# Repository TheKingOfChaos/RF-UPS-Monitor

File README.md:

# RF-UPS-Monitor

A mains power monitor built on a Raspberry Pi Pico with a W5500 Ethernet module. It reports whether mains power is present over SNMP v1 and v2c, including traps, together with standard interface statistics (IF-MIB) and the board temperature, so it can be monitored by LibreNMS or any other SNMP manager. It is configured through a menu on the USB serial port.

Current version: **2.4.2** (see [CHANGELOG.md](CHANGELOG.md)).

## Overview

- **Mains side:** an isolated detector (optocoupler with filtering) turns mains presence into a clean 3.3 V level on GPIO27. In the test setup an IKEA smart plug in front of it lets the tests switch mains off and on.
- **Board:** the Pico's core 1 samples GPIO27 and the reset button (GPIO22) every millisecond; core 0 runs the network, the SNMP agent and the serial menu. Settings live in the Pico's flash in two copies, and the W5500 provides 10/100 Ethernet over SPI.
- **Network:** the device gets its address by DHCP (or a static IP), is reachable as `rf-ups-monitor.local` (mDNS), answers SNMP v1/v2c on UDP 161 for LibreNMS or net-snmp, sends traps on UDP 162, and serves a configuration web page with login on TCP 80 ([Web page](#web-page)).
- **PC:** the USB serial port carries the configuration menu and the hardware-in-the-loop tests.

More diagrams (firmware architecture, SNMP request flow, mains flow, settings, tests) are in [docs/diagrams/](docs/diagrams/README.md).

## Status

| Feature | State |
|---|---|
| Ethernet with DHCP (default) or static IP | Working |
| Serial menu for network configuration | Working |
| Settings stored in flash, power-cut safe | Working |
| Factory reset button (GPIO22, 10 s hold, non-blocking, LED feedback) | Implemented; manual test with the real button pending |
| Mains power monitoring on GPIO27 (core 1, debounced) | Working, verified with real mains loss/restore (automated with a smart plug) |
| SNMP v1 and v2c agent (Get, GetNext, GetBulk, walk, bulkwalk) | Working, tested with net-snmp |
| SNMP traps in v1 or v2c (coldStart, authenticationFailure, mainsPowerLost/Restored) | Working, mains traps verified with real mains |
| SNMP rate limiting and access log | Working |
| Web page with login: status, DHCP/static IP, SNMP community, hostname, restart | Working |
| Hostname for SNMP sysName, DHCP and mDNS (`name.local`) | Working |
| Web interface can be turned off (serial menu or the page itself) | Working |
| IPv6 (dual stack): SNMP, web page and mDNS over IPv6, SLAAC, per-address rate limiting | Working |
| Static IPv6 address and gateway (serial menu or web page), next to SLAAC | Working |
| SNMP trap destination from DHCP option 224 | Working, tested with Kea 2.2.0; in your network once the DHCP server has option 224 |
| Interface statistics (IF-MIB ifTable/ifXTable, 64-bit counters) | Working, counted by the firmware |
| Board temperature (RP2040 internal sensor) | Working |
| LibreNMS OS definition (mains state, temperature, change counter) | Working, tested with LibreNMS 26.9.1 |

See [TODO.md](TODO.md) for the detailed plan.

## Documentation

| Document | Contents |
|---|---|
| This README | Hardware, wiring, serial menu, web page, network, IPv6, mains monitoring, factory reset, settings, building, SNMP overview, troubleshooting |
| [docs/MIB.md](docs/MIB.md) | Every SNMP object (system, IF-MIB, RF-UPS-MONITOR-MIB), traps, v1/v2c differences, rate limiting, errors, limits |
| [docs/LIBRENMS.md](docs/LIBRENMS.md) | Monitoring the device with LibreNMS: install, sensors, alerts, traps, Docker test setup |
| [docs/TESTING.md](docs/TESTING.md) | Test layers, how to run them, automated mains tests with a smart plug, what each suite covers |
| [CHANGELOG.md](CHANGELOG.md) | What changed in each version |
| [hardware/pico-poe-mains-carrier/](hardware/pico-poe-mains-carrier/README.md) | Carrier PCB (KiCad 10): circuit, isolation, mounting, fab files for JLCPCB, 3D models |
| [docs/diagrams/](docs/diagrams/README.md) | Excalidraw diagrams (editable) of the system, firmware, SNMP, mains flow, settings and tests |
| [.clinerules](.clinerules) | Project and test rules |

## Hardware

- Raspberry Pi Pico (RP2040) with a W5500 Ethernet module on SPI0, or the WIZnet **W5500-EVB-Pico-PoE**, which has both on one board (same pins) and is powered over PoE
- Mains detection circuit on GPIO27 (must be galvanically isolated, 3.3 V max)
- Factory reset push button from GPIO22 to GND
- USB cable for flashing and the serial menu (and for power without PoE)

### Carrier board

[hardware/pico-poe-mains-carrier/](hardware/pico-poe-mains-carrier/README.md) is a 2-layer carrier PCB (KiCad 10, 80 x 51.5 mm) for the W5500-EVB-Pico-PoE; the module is soldered flat by its castellated edges or plugged into two 1x20 female headers. It carries the isolated mains detector: 230 VAC on a screw terminal, a T 100 mA fuse, four 68 k 200 V resistors, an LTV-814S AC optocoupler (5 kVrms), an RC that bridges the zero crossings and a 74LVC1G14 Schmitt inverter driving GPIO27 (HIGH = mains present) and two LEDs (green = mains on, red = off, without firmware). It also has a TMP1075 temperature sensor on I2C0 and the factory reset button on GPIO22. Mains copper keeps at least 6.5 mm clearance and 6.4 mm creepage to the low-voltage side, enforced as DRC rules, with a slot under the optocoupler. Gerbers, BOM and placement files for JLCPCB, the schematic PDF and STEP/GLB models are in [hardware/pico-poe-mains-carrier/fab/](hardware/pico-poe-mains-carrier/fab/README.md) and `3d/`; `tools/generate.py` generates the whole KiCad project.

How the carrier and the firmware fit together:

| | Carrier | Firmware |
|---|---|---|
| Mains detection | MAINS_OK on GP27, HIGH = present | GPIO27, HIGH = present: matches |
| W5500 | On the module, GP16-GP21 | `include/pins.h` GP16-GP21: matches |
| Power | PoE through the module, 3V3(OUT) feeds the carrier | No dependency |
| Temperature | TMP1075 on I2C0 (GP4 SDA, GP5 SCL, address 0x48) | Not read yet: boardTemperature is the RP2040's internal sensor (TODO) |
| Factory reset button | SW1 from GP22 to GND, below the module (board v1.1) | Reads GPIO22 with the internal pull-up, hold 10 s: matches |
| Mains loss timing | The RC holds the signal about 30-50 ms after mains is lost (bridges zero crossings) | The firmware sees the loss that much later; `.clinerules` asks for 10 ms (TODO) |

### Pin configuration

All assignments are in [include/pins.h](include/pins.h).

| Pin | Function | Notes |
|---|---|---|
| GPIO16 | W5500 MISO | SPI0 RX |
| GPIO17 | W5500 CS | |
| GPIO18 | W5500 SCK | |
| GPIO19 | W5500 MOSI | SPI0 TX |
| GPIO20 | W5500 RST | Pulsed low at boot |
| GPIO21 | W5500 INT | Interrupt-driven receive |
| GPIO4 / GPIO5 | I2C0 SDA / SCL | TMP1075 on the carrier board, address 0x48; not used by the firmware yet |
| GPIO22 | Factory reset | Active low, internal pull-up |
| GPIO27 | Mains power detection | HIGH = power present, internal pull-down |
| LED | Onboard LED | Status / reset feedback |

## Serial menu

Connect to the Pico's USB serial port (`COM16` here) at **115200 baud, 8N1**, with PuTTY or any terminal. The menu appears right after boot, without waiting for the network; a `Network up after ... ms` message follows when the address is obtained. Press `?` and Enter to show the menu again.

```
=== RF-UPS-Monitor Menu ===
1. Show status
2. Use DHCP
3. Set static IP
4. SNMP settings
5. Access log
6. Web password
7. New default web password
8. Web interface on/off
9. Static IPv6
?. Show this menu
>
```

**1. Show status** prints the mains power state, the board temperature, the Ethernet link speed, traffic and drop counters, the SNMP counters and settings (community, sysName, sysContact, sysLocation), the configured network mode, the stored static settings, and the live interface: state, MAC, IP, subnet, gateway and DNS.

```
> 1

Mains power: present (22 changes, last change 1053 s ago)
SNMP: 802 packets, 802 responses (get 437, getnext 0, set 0), bad community 0, bad version 0, malformed 0
SNMP v2c: 792 requests, 365 getbulk
Board temperature: 40.4 C
Ethernet: link up, 100 Mbit/s, in 184054263 bytes / 1351415 packets, out 149671 bytes / 1002 packets
Ethernet drops: 0 discarded (no buffer), 0 errors, 211829 unknown protocol, 0 send errors
SNMP security: 0 rate limited, 0 access log events
SNMP community: "public"
sysName: "rf-ups-monitor"
sysContact: ""
sysLocation: ""
Trap destination: "" (4 sent, 0 failed)
Trap destination source: fixed (menu option 4)
Trap version: v2c
Hostname: rf-ups-monitor (DHCP, mDNS rf-ups-monitor.local)
Web interface: on (TCP port 80)
Web login: user admin, default password "k7wqz3mtd9" (change with option 6)
Core 0 stack: 2520 bytes never used
Mode: DHCP
Stored static IP: 10.10.6.249 / 255.255.0.0, gateway 10.10.0.1
Stored static IPv6: fd16:d833:4f0e:3ece::249/64, gateway from router advertisements
Live interface:
State: connected
MAC: 1E:B2:CF:4E:A2:2C
IP: 10.10.6.111
Subnet: 255.255.0.0
Gateway: 10.10.0.1
IPv6: FE80::1CB2:CFFF:FE4E:A22C
IPv6: FD16:D833:4F0E:3ECE::249 (static)
IPv6: FD16:D833:4F0E:3ECE:1CB2:CFFF:FE4E:A22C
IPv6 gateway: from router advertisements
DNS: 10.10.0.1
```

"Unknown protocol" counts frames the device receives but does not use (IPv6, LLDP, spanning tree); on a busy LAN it grows steadily, which is normal.

The interface state line is one of:

| State | Meaning |
|---|---|
| `connected` | Address assigned, device reachable |
| `link up, waiting for DHCP lease` | Cable OK, no DHCP answer yet (keeps retrying) |
| `no Ethernet link, check cable` | No link on the W5500 port |
| `W5500 not detected, check wiring` | The Ethernet module did not respond at boot |

**2. Use DHCP** switches to DHCP after you confirm with `y`.

**3. Set static IP** asks for the IP address, subnet mask and gateway in turn. The value in brackets is the current one; press Enter to keep it.

```
> 3
Press Enter to keep the value in brackets.
IP address [192.168.1.100]: 10.10.6.250
Subnet mask [255.255.255.0]: 255.255.0.0
Gateway [192.168.1.1]: 10.10.0.1

New mode: Static 10.10.6.250 / 255.255.0.0, gateway 10.10.0.1
Save and reboot? (y/n): y
Settings saved. Rebooting...
```

Every value is checked before it is accepted, and a rejected value is asked for again:
- addresses must be four numbers 0-255 (`10.10.6.250`)
- the subnet mask must be contiguous (`255.255.252.0` is fine, `255.0.255.0` is not)
- the IP must not be the network or broadcast address of the subnet
- the gateway must be in the same subnet and differ from the IP

Nothing changes until you answer `y`. Changes are saved to flash and the device reboots to apply them. Answer `n` to cancel.

**4. SNMP settings** asks for the community string, the hostname (which is also the SNMP sysName, see [Hostname](#hostname)), sysContact, sysLocation and the trap destination in turn. Press Enter to keep the value in brackets, or type `-` to clear a value (for the trap destination: turn traps off).

```
> 4
Press Enter to keep the value in brackets, '-' to clear it.
Community [public]: s3cret
Hostname (sysName) [rf-ups-monitor]: ups-rack4
sysContact []: ops@example.com
sysLocation []: Server room, rack 4
Trap destination IP or dhcp []: 10.10.6.65
Trap version (1/2c) [2c]:

New SNMP settings: community "s3cret", sysName "ups-rack4", sysContact "ops@example.com", sysLocation "Server room, rack 4", trap destination "10.10.6.65", trap version v2c
Save? (y/n): y
SNMP settings saved and active
```

- Community: 1-31 printable ASCII characters. After saving, requests with the old community get no answer.
- Hostname (sysName): 1-32 letters, digits and `-`, not starting or ending with `-`; `-` does not clear it. Active immediately for DHCP and mDNS too.
- sysContact, sysLocation: 0-63 printable ASCII characters.
- Trap destination: an IPv4 address that receives traps on UDP 162, `-` for no traps, or `dhcp` to take it from DHCP option 224 (see [docs/MIB.md](docs/MIB.md#trap-destination-from-dhcp)). Choosing `dhcp` keeps the fixed address for switching back.
- Trap version: `1` (SNMPv1 Trap-PDU) or `2c` (SNMPv2-Trap, default).
- Saved to flash and active immediately, no reboot. A factory reset restores `public`, `rf-ups-monitor`, empty contact and location, no trap destination and v2c traps.

**5. Access log** lists the most recent rejected SNMP requests, newest first: wrong community, SNMPv3, malformed packets, rate-limited sources and SetRequests. Repeats from the same source are counted on one line:

```
Access log: 3 entries, 128 events since boot
  10.10.6.65      rate limited   x104    last 2 s ago
  10.10.6.65      bad version    x1      last 40 s ago
  10.10.6.80      bad community  x23     last 61 s ago
```

Each new entry is also printed on the serial port when it happens (`SNMP access: bad community from 10.10.6.80`).

**6. Web password** sets the password for the web page (see [Web page](#web-page)), or `-` returns to the device default password. The password is asked twice and shown as `*` while typing.

**7. New default web password** replaces the device default password with a new random one after you confirm with `y`, and shows it. Use it if the default password became known to someone else: the old one stops working at once (browsers logged in with it are logged out), and the new one is kept across restarts. An own password set with option 6 stays in use.

**8. Web interface on/off** switches the web page on or off after you confirm with `y`. Off closes TCP port 80, logs every browser out and stops announcing the page over mDNS; SNMP and the serial menu are not affected. The setting is kept across restarts; a factory reset turns the web interface on again. Turning it on takes effect at once; the status screen shows `Web interface: on (TCP port 80)`.

**9. Static IPv6** asks for a static IPv6 address and an optional IPv6 gateway. Enter keeps the value in brackets, `-` removes it. The address is always a /64 and is added next to the link-local and SLAAC addresses; it is independent of DHCP/static IPv4.

```
> 9
The address is used as a /64 next to the automatic (SLAAC) address.
Press Enter to keep the value in brackets.
Static IPv6 address, '-' for none []: fd16:d833:4f0e:3ece::249
IPv6 gateway, '-' for routers that announce themselves []:

New static IPv6: fd16:d833:4f0e:3ece::249/64, gateway from router advertisements
Save and reboot? (y/n): y
Settings saved. Rebooting...
```

- Address: a global (`2001:db8:...`) or ULA (`fd..`) unicast address, written without `/64`; not link-local (`fe80::`, made automatically), multicast, `::1`, IPv4-mapped, or with an all-zero interface id (`prefix::`). It is stored in the short form (`FD16:0:0:0:0:0:0:249` becomes `fd16::249`).
- Gateway: optional. Empty: the device uses the routers that announce themselves (router advertisements). Set: every off-link IPv6 destination goes through it; it must be link-local (`fe80::1`, usual for routers) or in the address's /64.
- Saved to flash; the device reboots to apply it. A factory reset removes it.

If you lock yourself out with a wrong static address, use the serial menu to switch back to DHCP, or do a factory reset.

## Web page

The device serves a small configuration page on **http://&lt;device IP&gt;/** (port 80): log in, see the status, change the network settings (IPv4 and static IPv6), the hostname and the SNMP community, restart the device, or turn the page off. It is also reachable as **http://rf-ups-monitor.local/** (mDNS, see [Hostname](#hostname)) and over IPv6 as **http://[&lt;IPv6 address&gt;]/**. Everything on the page can also be done in the serial menu.

- **Login:** user `admin`. Until you set your own password, the password is the device's **default password**: 10 random characters generated on first boot, different for every device, and shown only on the serial status screen (menu option 1): `Web login: user admin, default password "k7wqz3mtd9"`. A factory reset does not change it; menu option 7 replaces it with a new random one.
- **Own password:** serial menu option 6 sets one (8-32 characters, no spaces; typed characters are shown as `*`), or `-` goes back to the device default. Changing it logs every browser out. The password is stored as a salted SHA-256 hash (2000 rounds), never as text; checking it takes about half a second, done in small steps so SNMP keeps answering meanwhile. It can only be changed from the serial menu, so someone who learns it cannot lock you out.
- **Status:** mains power (green or red badge) and change count, uptime, board temperature, Ethernet link, hostname and `.local` name, IP address, IPv6 address and link-local address (when the device has them), MAC address, network mode, static IPv6 address (when set), firmware version (top bar).
- **Device name:** the hostname (also SNMP sysName and mDNS name), active immediately.
- **Network:** DHCP or static IP (address, mask and gateway are checked as in the serial menu). Saving restarts the device; the page tells you the new address.
- **IPv6:** static IPv6 address and gateway, checked as in the serial menu (option 9); empty fields remove them. Saving restarts the device.
- **SNMP community:** active immediately, no restart.
- **Restart device** and **Log out** buttons.
- **Web interface: Turn off…** asks for confirmation, then turns the web page off. Only serial menu option 8 (or a factory reset) turns it on again.

The page carries the RF logo (`logo/RF-canopy-RGB-Orange.svg`) in the top bar and on the login card, and as the browser tab icon (`/favicon.svg`).

The page is styled with [Bootstrap](https://getbootstrap.com/) 5.3.3, which is built into the firmware: the device serves its CSS from flash (31 KB, gzip-compressed, cached by the browser for a year), so the page looks the same on a management network without internet access. It works on phones too. `scripts/embed_bootstrap.py` downloads a pinned version, checks it against Bootstrap's official integrity hash and regenerates `lib/web_ui/src/bootstrap_css.cpp`.

Security:
- Five wrong logins in a row lock the login for 30 seconds, from any address. Failed logins and lockouts appear in the access log (menu option 5) as `web login failed` / `web locked out`.
- A session ends after 15 minutes without a request, on Log out, after a restart, or when the password changes. At most two browsers are logged in at once.
- The session cookie is `HttpOnly` and `SameSite=Strict`, every form carries a per-session token (CSRF protection), and the page sends a strict Content-Security-Policy (no scripts at all) and forbids framing.
- **Plain HTTP:** the password and the session cookie cross the network unencrypted, like the SNMP community. Use the page on a trusted management network.
- Settings changed on the page are saved to flash like those from the serial menu, and are written to the serial log (`Web: network settings saved ...`).
- The server handles one connection at a time without ever blocking: requests are read as they arrive (at most 2 KB), responses are written as fast as the network takes them, and a connection that does not finish within 5 seconds is closed. SNMP keeps answering in between.

Pages and forms, for scripts (e.g. `curl` with a cookie jar). Every POST except `/login` needs the session cookie `sid` and the form field `csrf` with the token from the page (`name="csrf" value="..."`); forms are `application/x-www-form-urlencoded`.

| Path | Method | Fields | Does |
|---|---|---|---|
| `/` | GET | | Login form, or the status and settings page when logged in |
| `/login` | POST | `user`, `password` | Logs in; sets the `sid` cookie and redirects to `/` |
| `/logout` | POST | | Ends the session |
| `/network` | POST | `mode` (`dhcp` or `static`), `ip`, `mask`, `gateway` | Saves IPv4 settings and restarts |
| `/ipv6` | POST | `ipv6`, `ipv6gw` (empty = none) | Saves the static IPv6 address and gateway and restarts |
| `/hostname` | POST | `hostname` | Saves the hostname (sysName, DHCP, mDNS), active immediately |
| `/community` | POST | `community` | Saves the SNMP community, active immediately |
| `/reboot` | POST | | Restarts the device |
| `/disable` | POST | `confirm=yes` (without it: the confirmation page) | Turns the web interface off |
| `/favicon.svg` | GET | | The logo, no login |
| `/static/bootstrap-5.3.3.min.css` | GET | | The stylesheet (gzip), no login |

Responses: `400` with the reason on the page for an invalid value (nothing is saved), `403` without a valid session or CSRF token, `429` while logins are locked, `413` for a request over 2 KB.

## Network

- **DHCP** is the default. The lease is requested in the background, so boot and the menu never wait for it. If no DHCP server answers, the device keeps retrying indefinitely and does not fall back to another address (to avoid IP conflicts). Lease renewal is automatic, and the serial log reports when the address is obtained, changes or is lost.
- **Static IP** is set through the serial menu.
- The MAC address is derived from the Pico's unique chip ID, so it is stable across reboots. Reserve it in your DHCP server for a fixed address.
- Networking uses the Arduino-Pico core's lwIP driver for the W5500 (`Wiznet5500lwIP`).

## Hostname

The device has one name, the **hostname** (default `rf-ups-monitor`), used in three places:

- **SNMP sysName**: LibreNMS and other managers show it as the device name.
- **DHCP**: sent to the DHCP server with every request (option 12), so the lease list of your router shows the name.
- **mDNS**: the device answers as **`<hostname>.local`**, so `http://rf-ups-monitor.local/` and `snmpwalk -v2c -c public rf-ups-monitor.local` work without knowing the IP address (Windows 10 and later, macOS, Linux with Avahi; not from inside WSL with its default NAT networking, where mDNS from the LAN does not arrive). The web page is also announced as an `_http._tcp` service.

Set it with menu option 4 (first question after the community) or on the web page. It must be 1-32 letters, digits and `-`, not starting or ending with `-`. A change applies immediately: mDNS announces the new name and the DHCP lease is renewed with it; no restart.

A sysName set with older firmware may contain spaces or other characters; it is kept as it is, and the device uses a cleaned-up version for DHCP and mDNS (`Server room UPS` becomes `Server-room-UPS`). The status screen shows the name in use: `Hostname: rf-ups-monitor (DHCP, mDNS rf-ups-monitor.local)`.

## IPv6

The device runs IPv4 and IPv6 side by side (dual stack):

- **Addresses:** a link-local address (`fe80::`, from the MAC as EUI-64) always, a global or ULA address from the router's advertisement (SLAAC) when the LAN has an IPv6 router, and optionally a static address (below). The status screen lists them (`IPv6: FD16:D833:4F0E:3ECE:1CB2:CFFF:FE4E:A22C`), the web page shows them in the status table.
- **Static address:** serial menu option 9 or the web page set one static IPv6 address (always /64) and an optional gateway. It is added next to SLAAC, not instead of it, and goes through duplicate address detection: if another host already uses it, the status screen says `(DUPLICATE: another host uses it, not in use)`. With a gateway set, all off-link IPv6 traffic goes through it (it overrides routers from advertisements); without one, the advertised routers are used. Takes effect after the restart that saving triggers.
- **SNMP** answers over IPv6 on UDP 161 like over IPv4 (replies up to 1452 bytes, one Ethernet frame: the device does not fragment IPv6 packets), e.g. `snmpget -v2c -c public udp6:[fd16:d833:4f0e:3ece:1cb2:cfff:fe4e:a22c] 1.3.6.1.2.1.1.1.0`. LibreNMS polls it over IPv6 when added with transport `udp6` (tested with LibreNMS 26.9.1, see [docs/LIBRENMS.md](docs/LIBRENMS.md#ipv6)).
- **Web page:** `http://[<IPv6 address>]/`; **mDNS:** `rf-ups-monitor.local` resolves to the IPv6 address too.
- **Rate limiting and access log:** per full source address, as for IPv4; the access log shows the address (`fd16:d833:4f0e:3ece:9000:9aaa:490a:3189`). Not per /64: on a LAN every host shares one /64, and a manager's trust must not pass to its neighbours. A host that rotates through many IPv6 addresses is held by the shared limit for untrusted sources, like faked IPv4 addresses.
- **Still IPv4 only:** traps (the trap destination is an IPv4 address; v1 traps cannot carry an IPv6 agent address anyway), DHCP option 224, and the IP and IF tables in the MIB stay as they are. There is no DHCPv6 address assignment.

Turning IPv6 off needs a firmware build without `PIO_FRAMEWORK_ARDUINO_ENABLE_IPV6` in `platformio.ini`.

## Mains power monitoring

GPIO27 reads the mains detection circuit: HIGH = mains present, LOW = mains lost. The internal pull-down is enabled, so a disconnected input reads as "lost" rather than floating.

- Core 1 samples the pin every millisecond and only accepts a new level once it has held for 5 ms, so short glitches and contact bounce are ignored. A real change is detected within 6 ms (requirement: 10 ms).
- Core 0 (network, menu, SNMP) reads the state through a sequence lock, so it never sees a half-updated value and core 1 never waits.
- Every change is logged on the serial port, e.g. `Mains power LOST at 123456 ms`, and the status screen shows the state, the number of changes and the time since the last one:

```
Mains power: present (2 changes, last change 37 s ago)
```

The input must be a clean DC level from an isolated circuit (optocoupler with filtering). An unfiltered optocoupler on AC toggles at 100 Hz and would be read as constant power loss and restore; `pio test -e pico -f embedded/test_mains_input -v` prints the raw toggle rate to check this. On the current hardware it reads 0 toggles/s.

## Factory reset

1. Press and hold the button on GPIO22. The onboard LED blinks slowly (2 Hz) while it is held, and the serial log prints `Factory reset button pressed`.
2. After 10 seconds the LED blinks fast, and the log prints `Factory reset after 10000 ms hold`. You can release the button.
3. Settings return to defaults: DHCP on (stored static IP back to `192.168.1.100`), no static IPv6 address, community `public`, sysName `rf-ups-monitor`, empty sysContact and sysLocation, no trap destination (fixed), the web interface on, and the web page back on the device default password (the default password itself stays the same).
4. The device reboots, well within 2 seconds of the trigger.

Releasing the button earlier cancels the reset (`released after ... ms, no reset`). The device keeps working normally while the button is held: SNMP answers, the menu responds and mains monitoring continues. A button held down while the device starts is ignored until it has been released once, so a stuck button cannot cause a reset loop.

## Settings storage

Settings are stored as JSON on the Pico's internal flash (LittleFS) in two copies, `data/settings_a.json` and `data/settings_b.json`:

```json
{"community":"public","dhcpEnabled":true,"staticIP":"192.168.1.100",
 "subnetMask":"255.255.255.0","gateway":"192.168.1.1","ipv6Address":"","ipv6Gateway":"",
 "sysName":"rf-ups-monitor","sysContact":"","sysLocation":"","trapTarget":"",
 "trapVersion":2,"trapFromDhcp":false,"webEnabled":true,"webPassword":"","version":1,"sequence":7}
```

| Field | Meaning |
|---|---|
| `community` | SNMP community string, 1-31 printable characters |
| `sysName` | Hostname and SNMP sysName (new values: a valid hostname; older free text still loads); optional, default `rf-ups-monitor` |
| `sysContact`, `sysLocation` | SNMP system group text, 0-63 printable characters; optional, default empty |
| `trapTarget` | IPv4 address that receives traps, empty = no traps; optional |
| `trapVersion` | `1` = SNMPv1 Trap-PDU, `2` = SNMPv2-Trap (default); optional |
| `trapFromDhcp` | `true` = trap destination from DHCP option 224 (`trapTarget` is kept for switching back); optional, default `false` |
| `webEnabled` | `false` = web interface off; optional, default `true` |
| `webPassword` | Salted SHA-256 hash of the web password (`<salt>$<hash>`), empty = device default password; optional |
| `dhcpEnabled` | `true` = DHCP, `false` = use the static fields |
| `staticIP`, `subnetMask`, `gateway` | Static configuration, validated when DHCP is off |
| `ipv6Address`, `ipv6Gateway` | Static IPv6 address (/64) and gateway, short form, empty = none; independent of `dhcpEnabled`; optional |
| `version` | Layout version, currently 1 |
| `sequence` | Save counter |

Each save writes the copy that is **not** in use, with `sequence` one higher, and reads it back to check it. At boot the valid copy with the highest `sequence` is used. If the device loses power during a save, the half-written copy fails validation and the previous one is loaded, so settings are never lost. If neither copy is valid, factory defaults are saved.

Files from older firmware (without `sequence`, with an `active_file` pointer) are still loaded, and the pointer file is removed.

The project's `data/` folder is **not** needed: the firmware creates its settings on first boot. Uploading it (`pio run -t uploadfs`) replaces the whole flash filesystem and erases the device's settings.

## Building and flashing

Requirements: VS Code with PlatformIO. On Windows you also need the WinUSB driver on the Pico's boot interface, a one-time step with Zadig described in [docs/TESTING.md](docs/TESTING.md#usb-driver-for-flashing).

```powershell
$pio = "$env:USERPROFILE\.platformio\penv\Scripts\pio.exe"
& $pio run -e pico               # build
& $pio run -e pico -t upload     # build and flash (close PuTTY first)
& $pio device monitor            # serial monitor
```

If upload fails, hold BOOTSEL while plugging in the Pico and copy `.pio\build\pico\firmware.uf2` to the `RPI-RP2` drive.

## Testing

There are three layers: unit tests on the PC, tests on the Pico, and hardware-in-the-loop tests that drive the real serial menu.

```powershell
& $pio test -e native     # PC, no hardware
& $pio test -e pico       # on the Pico (reflash the firmware afterwards)
& "$env:USERPROFILE\.platformio\penv\Scripts\python.exe" -m unittest discover -s test/hil -v
```

Setup, coverage and how to add tests: [docs/TESTING.md](docs/TESTING.md). Rules for test code: [.clinerules](.clinerules).

## Project structure

```
include/pins.h              GPIO assignments
include/version.h           Firmware version (FIRMWARE_VERSION)
include/lwip_hooks.h        lwIP hook: static IPv6 gateway as next hop
src/main.cpp                Boot, Ethernet bring-up, main loop
src/cli.cpp                 Serial menu
src/factory_reset.cpp       Reset button on core 1, reset on core 0
src/web_service.cpp         Web page on TCP 80: non-blocking connection handling, default password
src/stack_watch.cpp         Core 0 stack high-water mark for the status screen
src/hostname.cpp            Hostname for DHCP and mDNS (name.local), applied without restart
src/source_key.h            Source address -> rate-limit key (full IPv4 or IPv6 address)
src/ipv6_static.cpp         Static IPv6 address and gateway (lwIP hook in include/lwip_hooks.h)
src/diag.cpp                Hang diagnosis build (-DRFUPS_DIAG): watchdog, crash and panic capture
lib/netconfig/              IPv4/IPv6 parsing, formatting and validation, hostnames (pure C++)
lib/settings_codec/         Settings JSON, validation, A/B selection (pure C++)
lib/settings/               LittleFS storage on top of settings_codec
lib/power_monitor/          Mains input debouncer, reset button logic (pure C++)
lib/access_control/         Rate limiter and access log, IPv4 and IPv6 sources (pure C++)
lib/mains_input/            GPIO27 sampler on core 1, seqlock hand-over to core 0
lib/snmp_ber/               ASN.1 BER codec and OIDs for SNMP (pure C++)
lib/snmp_agent/             SNMP v1/v2c messages, MIB, request handling, traps (pure C++)
lib/if_stats/               Ethernet frame counting and W5500 PHY status decoding (pure C++)
lib/web_ui/                 Web page: HTTP parser, login, sessions, pages, SHA-256, logo (pure C++)
lib/dhcp_option/            Ask for and read DHCP option 224 in Ethernet frames (pure C++)
src/snmp_service.cpp        UDP port 161, device state for the MIB
src/net_stats.cpp           Counts frames at the lwIP driver, reads the W5500 PHY register
src/board_temp.cpp          RP2040 die temperature, averaged
mibs/                       RF-UPS-MONITOR-MIB
hardware/                   Carrier PCB for the W5500-EVB-Pico-PoE (KiCad project, fab files, 3D, renders)
logo/                       RF logo (SVG), used on the web page
librenms/                   LibreNMS OS detection and discovery definitions, Docker test setup
test/host/                  Host build of the agent for net-snmp checks
test/native/                Unit tests, run on the PC
test/embedded/              Unity tests, run on the Pico
test/hil/                   Python tests over the serial port
scripts/wait_for_port.py    Waits for the USB port after flashing, for pio test
scripts/embed_bootstrap.py  Embeds Bootstrap's CSS (pinned, integrity-checked) in lib/web_ui
scripts/sanitize.sh         Native tests under ASan/UBSan (run in WSL)
scripts/host_agent_check.sh Agent against real net-snmp tools, no hardware (run in WSL)
docs/TESTING.md             Test guide
docs/MIB.md                 SNMP objects, traps, errors, limits
docs/LIBRENMS.md            Adding the device to LibreNMS
docs/diagrams/              Excalidraw diagrams and their SVGs (make_diagrams.py)
CHANGELOG.md                Release history
.github/workflows/tests.yml CI: unit tests, sanitizers, net-snmp check, firmware build
```

Pure libraries have no Arduino or hardware dependency so they can be unit tested on the PC. Hardware and file access stay in thin layers on top.

## SNMP

An SNMP agent runs on UDP port 161 and answers SNMPv1 and SNMPv2c, each request in its own version (SNMPv3 is not supported). The community is `public` by default (menu option 4 changes it, along with sysName, sysContact and sysLocation). It supports Get and GetNext, so `snmpwalk` works, and in v2c GetBulk, so `snmpbulkwalk` works too; everything is read-only.

```
.1.3.6.1.2.1.1          system group
  .1.0  sysDescr        .2.0  sysObjectID     .3.0  sysUpTime
  .4.0  sysContact      .5.0  sysName         .6.0  sysLocation
  .7.0  sysServices
.1.3.6.1.2.1.2          IF-MIB interfaces: ifNumber and ifTable for the Ethernet port (index 1)
.1.3.6.1.2.1.31.1.1     IF-MIB ifXTable: ifName, 64-bit ifHC* counters (v2c only), ifHighSpeed
.1.3.6.1.4.1.63050      RF-UPS-MONITOR-MIB (enterprise 63050)
  .1.0  mainsPowerStatus      INTEGER 1 = present, 0 = lost
  .2.0  mainsPowerChanges     Counter32
  .3.0  mainsPowerLastChange  TimeTicks
  .4.0  boardTemperature      Integer32, 0.1 degrees Celsius
```

The interface counters are kept by the firmware: every Ethernet frame the W5500 receives or sends is counted (octets, unicast, multicast, broadcast), since the W5500 in MAC-raw mode has no counters of its own. Link state and speed come from the W5500 PHY register. The board temperature is the RP2040's internal sensor, which reads the chip temperature: a few degrees above the air around it.

To monitor the device with LibreNMS see [docs/LIBRENMS.md](docs/LIBRENMS.md).

```bash
snmpwalk     -v1  -c public 10.10.6.111
snmpbulkwalk -v2c -c public 10.10.6.111
snmpget      -v2c -c public 10.10.6.111 1.3.6.1.4.1.63050.1.0
```

**Traps** go to the trap destination set in menu option 4 (UDP 162), as v2c (default) or v1: `coldStart` at boot, `mainsPowerLost` and `mainsPowerRestored` (with the three mains objects), and `authenticationFailure` for a wrong community (at most one per 10 s).

GetBulk replies hold at most 16 objects, so a small request cannot be used to reflect a large reply at a faked source address.

**Security:** each source address may send 50 requests per second on average, with bursts of 100. Sources that have not shown the right community share a limit of 100 per second, so faked source addresses cannot get around it or starve your managers; managers that use the community share a separate limit of 200 per second. More is dropped and logged. Change the community from `public` (menu option 4): SNMPv1 and v2c have no other authentication. Rejected requests are kept in the access log (menu option 5).

Object details, traps, error behaviour, limits and the MIB file: [docs/MIB.md](docs/MIB.md). The status screen (menu option 1) shows the SNMP counters, rate-limited requests and traps sent.

## Troubleshooting

| Problem | What to check |
|---|---|
| Someone else knows the default web password | Serial menu option 7 makes a new one; or set your own with option 6 |
| Web page does not answer at all (connection refused) | The web interface may be off: status screen "Web interface: off", turn it on with menu option 8 |
| Traps go nowhere with trap destination `dhcp` | Status screen "Trap destination source": the DHCP server must have option 224 configured |
| Forgot the web password | Serial menu option 6, enter `-` to go back to the device default password shown on the status screen |
| Web page does not load | Use `http://` (not https); the status screen shows the device IP |
| Web page says "Too many failed logins" | Five wrong passwords in a row lock the login for 30 s; wait and use the password from the status screen (or your own from option 6) |
| Web page says "Form expired" or "Not logged in" | The session ended (15 min idle, restart, password change, or a third browser logged in) or the page was old: reload it and log in again |
| Device restarts after saving on the web page | Network and IPv6 settings need a restart; it is expected. Find the new address on the status screen if it changed |
| No traps arrive | Trap destination set (status screen shows it and "N sent"); firewall on the receiving PC must allow inbound UDP 162 |
| A manager gets no answers after polling hard | Rate limit (50/s per source): check menu option 5 for "rate limited" |
| No IP address | Menu option 1 shows the state: cable/link, or no DHCP answer (it keeps retrying) |
| Unreachable after setting static IP | Use the serial menu to check or switch back to DHCP, or factory reset |
| Upload fails with "Access denied" | Close PuTTY or the serial monitor |
| Upload fails with "unable to connect" in BOOTSEL | Install the WinUSB driver with Zadig |
| No serial output | Terminal must set DTR (PuTTY does); reset the board |

## Safety

- The mains detection circuit must be galvanically isolated (optocoupler). The carrier board's isolation (clearance, creepage, slot) is described in its [README](hardware/pico-poe-mains-carrier/README.md#isolation).
- Mains wiring must be done by a qualified person, in a closed enclosure, with the supply fused upstream.
- No GPIO may see more than 3.3 V.
- Ground all modules properly.

## License

MIT

The web page includes Bootstrap's CSS, Copyright 2011-2024 The Bootstrap Authors, MIT license (https://github.com/twbs/bootstrap/blob/main/LICENSE).

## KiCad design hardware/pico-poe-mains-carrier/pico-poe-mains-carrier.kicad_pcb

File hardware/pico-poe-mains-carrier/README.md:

# W5500-EVB-Pico-PoE mains monitor carrier

A 2-layer carrier board for the WIZnet W5500-EVB-Pico-PoE. It is 80 x 51.5 mm: exactly as long as the module, so both short edges line up with the module. The board extends 1.5 mm above the module for the solder fillets. It has 5x M3 holes, with centres at (4, 25.5), (4, 46) and (76, 46) mm from the module's top-left corner, plus H4 (30, 10.5) and H5 (66.5, 10.5) under the module, between the header rows.
All SMD parts are on the top side. The only through-hole parts are the module headers and the screw terminal.

## What it does

| Function | Connection |
|---|---|
| 230 VAC present / absent | **GP27** (module pin 32): HIGH = mains present, LOW = mains absent |
| LED indication (hardware, no firmware needed) | Green D1 = mains ON, red D2 = mains OFF |
| Temperature | TMP1075 on I2C0: **GP4 = SDA, GP5 = SCL**, address **0x48** |
| Factory reset | SW1 from **GP22** (module pin 29) to GND, below the module; hold 10 s (the firmware's internal pull-up holds GP22 high) |
| Power | From the module's 3V3(OUT) pin 36 (the module is PoE powered) |

GP16 to GP21 are used by the on-board W5500 and are not used here.

## Mounting the module

| Soldered flat | On female headers |
|---|---|
|  |  |
|  |  |

You can mount the module in either of two ways; the footprint supports both.

- **Socketed:** two 1x20 female headers (2.54 mm, 8.5 mm high, e.g. LCSC C2905423) in the through-hole pads, and two 1x20 male headers (2.5 mm body) soldered under the module. The module sits 11 mm above the carrier and stays removable. Use all five mounting holes: screw the carrier down through H4 and H5 first (a normal M3 pan or cheese head fits easily), then plug the module in.
- **Soldered flat:** the module's long edges are castellated, and every pin has a pad that reaches 1 mm past the module edge. Solder the castellations directly; no headers are needed. H4 and H5 are covered by the module and stay empty; mount the carrier by H1 to H3.

For flat mounting, the carrier has clearance for the parts that stick out under the module. The positions come from WIZnet's V1.1 drill file.
- A corner notch for the RJ45 pins, posts and shield tabs, and for the PoE module's first 1x4 header (x 20.4 mm).
- A window for the PoE module's second 1x4 header (x 55.0 mm) and the SWD header (x 58.5 mm).
- A notch at the USB end for the USB-C shell and its tabs, which reach 0.37 mm below the module.

Trim any header pins under the module flush before soldering it down.

## Circuit

- 230 VAC goes in on J1 (L/N, 5.08 mm screw terminal on the right edge; the wires enter from the same end as the USB port).
- F1 (Schurter UMT 250, T 100 mA, 250 VAC) follows J1 in L. The mains side is a single series loop (L, F1, R1, optocoupler, R4, R3, R2, N), so F1 carries any fault current on the board, whichever way L and N are wired. It does not replace the upstream fuse.
- Four 68 k 1206 resistors rated 200 V (R1 in L, R2 to R4 in N) limit the current to about 1.2 mA peak, about 50 mW per resistor.
- An LTV-814S AC-input optocoupler (5 kVrms) pulls SENSE low on both half-cycles.
- C1 (1 µF) with R5 (47 k) bridges the zero crossings, so SENSE goes high about 30 to 50 ms after mains is lost.
- A 74LVC1G14 Schmitt inverter produces a clean MAINS_OK signal. It drives GP27 and both LEDs.

## Isolation

The mains area is on the right, below the module's USB end, outlined on silkscreen ("DANGER 230VAC"). The low-voltage logic, LEDs and temperature sensor are on the left. MAINS_OK, +3V3 and I2C reach them on the bottom layer, running between the module's two header rows.

- Mains copper is at least 6.5 mm from everything else, with at least 6.4 mm creepage. Both are enforced as DRC rules in `pico-poe-mains-carrier.kicad_dru`.
- A routed slot under the optocoupler lengthens the creepage path.
- There is no copper pour and there are no vias inside the mains area.
- The mounting holes are well away from the mains area.

## Files

- `pico-poe-mains-carrier.kicad_pro/.kicad_sch/.kicad_pcb`: the KiCad 10 project
- `PicoPoE_Carrier.kicad_sym`, `PicoPoE_Carrier.pretty/`: project symbols and the module footprint
- `fab/`: Gerbers and drill (zip), BOM and CPL in JLCPCB format, schematic PDF, STEP model
- `tools/generate.py`: generates the whole project; `tools/check.sh` runs ERC and DRC; `tools/fab.sh` exports the fab files

## Assembly notes

- Socketed: fit 2x 1x20 female headers (not in the BOM). Flat: solder the castellated edges, no headers needed.
- The module (U1) is excluded from the BOM and CPL.
- F1 has no LCSC part number: order Schurter 3403.0156.11 through JLCPCB's global sourcing or solder it by hand (Mouser, DigiKey). SW1 is LCSC C318884.
- Check the rotation of U2, U3 and U4 in JLCPCB's placement preview before ordering.
- The temperature reading includes some self-heating from the board and module. For true ambient, mount the board vertically or add an offset in firmware.
- Mains wiring must be done by a qualified person. The board must sit in a closed enclosure, and the supply must be fused upstream.

## Firmware

The firmware in this repository (C++, see the [main README](../../README.md)) runs on the module unchanged: it reads MAINS_OK on GP27 (HIGH = mains present) and uses the on-board W5500 on GP16-GP21. It does not read the TMP1075 yet. Its 10 s factory reset reads SW1 on GP22 (active low).

## Firmware sketch (MicroPython)

```python
from machine import Pin, I2C
mains = Pin(27, Pin.IN)
i2c = I2C(0, sda=Pin(4), scl=Pin(5), freq=400_000)
raw = i2c.readfrom_mem(0x48, 0x00, 2)
temp_c = ((raw[0] << 8 | raw[1]) >> 4) * 0.0625   # sign-extend for < 0 C
print("mains", "ON" if mains.value() else "OFF", "temp", temp_c)
```

## Repository layout

```
pico-poe-mains-carrier/
├── pico-poe-mains-carrier.kicad_pro   KiCad 10 project
├── pico-poe-mains-carrier.kicad_sch   schematic
├── pico-poe-mains-carrier.kicad_pcb   PCB
├── pico-poe-mains-carrier.kicad_dru   custom design rules (230 VAC isolation)
├── PicoPoE_Carrier.kicad_sym          project symbol library
├── PicoPoE_Carrier.pretty/            project footprint library (module footprint)
├── sym-lib-table, fp-lib-table        project library tables (paths are relative)
├── fab/                               Gerbers, BOM, CPL, schematic PDF (see fab/README.md)
├── images/                            renders: top, bottom, 3D and side views; module soldered flat
│                                      (iso, side-flat), on headers (*-headers) and carrier only
├── 3d/                                STEP + GLB of the board with the module soldered flat and on
│                                      headers, STEP of the carrier only, and WIZnet's module model
└── tools/
    ├── generate.py                    generates the whole KiCad project
    ├── check.sh                       regenerate + ERC + DRC (needs kicad-cli 10)
    ├── fab.sh                         export the files in fab/
    ├── render.sh                      render images/ and export 3d/
    └── stock_fp/                      copies of the KiCad 10 library footprints used
```

All library paths are relative (`${KIPRJMOD}`), so the folder works anywhere. For example, you can place it at `hardware/pico-poe-mains-carrier/` in your firmware repository. Stock footprints and 3D models come from the standard KiCad 10 libraries.

`tools/generate.py` rewrites the schematic and PCB. If you edit the board by hand in KiCad, either copy the change into `generate.py` or stop using the generator; otherwise your edit will be overwritten.

`3d/W5500-EVB-Pico-PoE_V1.1.step` is WIZnet's 3D model of the module, from https://docs.wiznet.io/Product/Chip/Ethernet/W5500/W5500-EVB-Pico-PoE. The module footprint shows it soldered flat. The cutouts in the carrier match WIZnet's V1.1 drill file.

The footprints in `tools/stock_fp/` are from the KiCad library, licensed CC-BY-SA 4.0 with an exception for designs made with them (https://www.kicad.org/libraries/license/).

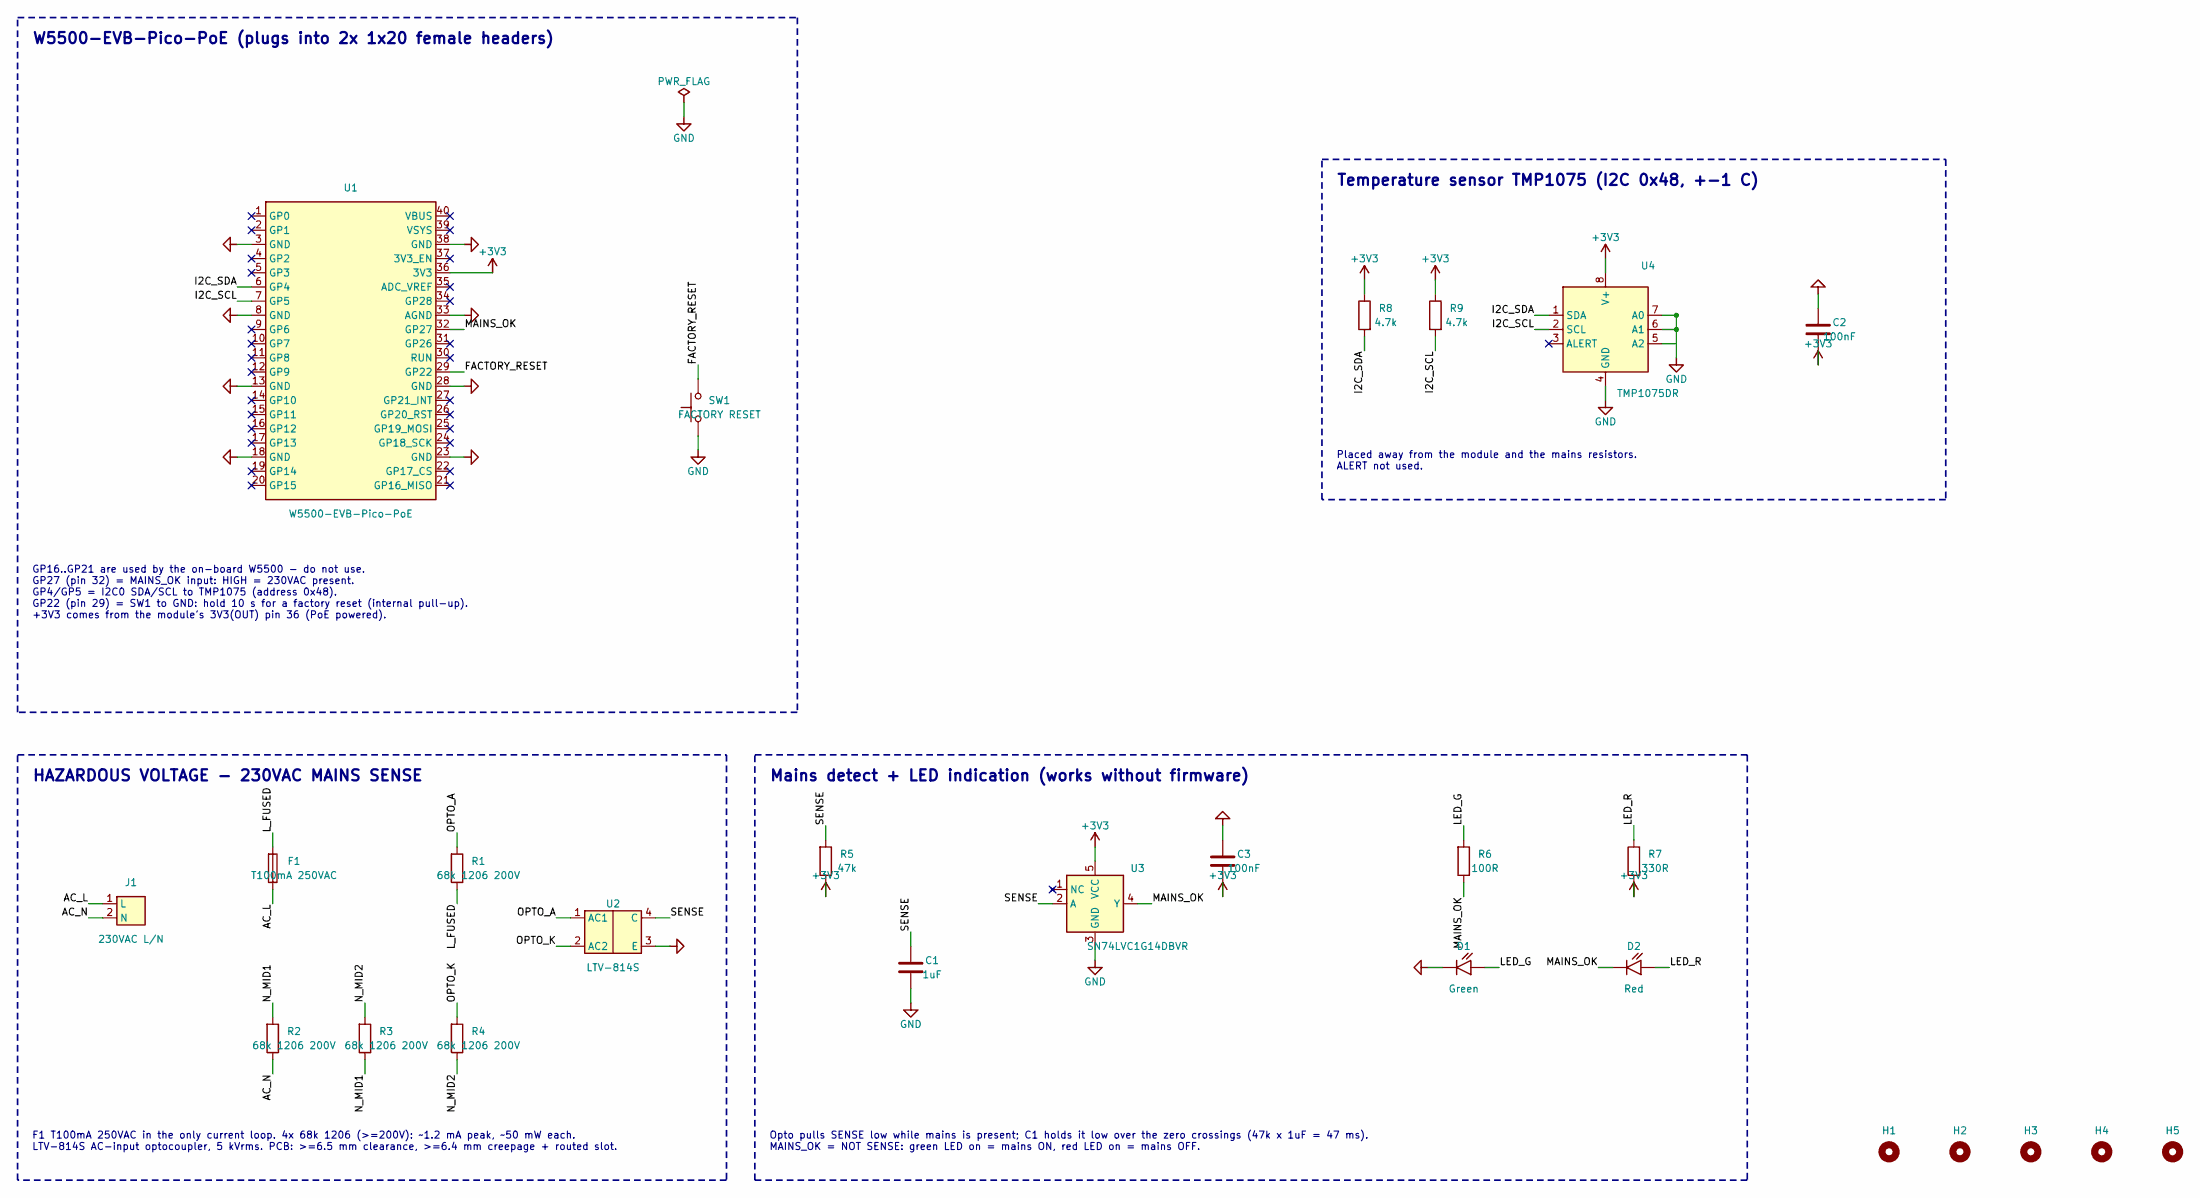
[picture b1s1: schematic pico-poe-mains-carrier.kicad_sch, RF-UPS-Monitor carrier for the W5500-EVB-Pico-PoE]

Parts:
C1: 1uF; C_0603_1608Metric; LCSC C15849
C2, C3: 100nF; C_0603_1608Metric; LCSC C14663
D1: Green; LED_0805_2012Metric; LCSC C2297
D2: Red; LED_0805_2012Metric; LCSC C84256
F1: T100mA 250VAC; Fuse_Schurter_UMT250; MPN Schurter 3403.0156.11 (UMT 250, T 100 m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
H1, H2, H3: MountingHole_3.2mm_M3
H4, H5: MountingHole_3.2mm_M3; MountingHole_3.2mm_M3_UnderModule
J1: 230VAC L/N; TerminalBlock_Phoenix_MKDS-1,5-2-5.08_1x02_P5.08mm_Horizont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; MPN Phoenix 1715721 (MKDS 1,5/2-5,08)
R1, R2, R3, R4: 68k 1206 200V; R_1206_3216Metric; LCSC C2889820
R5: 47k; R_0603_1608Metric; LCSC C25819
R6: 100R; R_0603_1608Metric; LCSC C22775
R7: 330R; R_0603_1608Metric; LCSC C23138
R8, R9: 4.7k; R_0603_1608Metric; LCSC C23162
SW1: FACTORY RESET; SW_Push_1P1T_XKB_TS-1187A; MPN XKB TS-1187A-B-A-B; LCSC C318884
U1: W5500-EVB-Pico-PoE; W5500-EVB-Pico-PoE_Socket; MPN W5500-EVB-Pico-PoE
U2: LTV-814S; SMDIP-4_W9.53mm; MPN LTV-814S-TA1; LCSC C125118
U3: SN74LVC1G14DBVR; SOT-23-5; LCSC C7835
U4: TMP1075DR; SOIC-8_3.9x4.9mm_P1.27mm; LCSC C2878381

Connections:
+3V3: C2.1, C3.2, R5.2, R7.1, R8.2, R9.2, U1.36 (3V3), U3.5 (VCC), U4.8 (V+)
/AC_L: F1.2, J1.1 (L)
/AC_N: J1.2 (N), R2.2
/FACTORY_RESET: SW1.1, U1.29 (GP22)
/I2C_SCL: R9.1, U1.7 (GP5), U4.2 (SCL)
/I2C_SDA: R8.1, U1.6 (GP4), U4.1 (SDA)
/LED_G: D1.2 (A), R6.1
/LED_R: D2.2 (A), R7.2
/L_FUSED: F1.1, R1.2
/MAINS_OK: D2.1 (K), R6.2, U1.32 (GP27), U3.4 (Y)
/N_MID1: R2.1, R3.2
/N_MID2: R3.1, R4.2
/OPTO_A: R1.1, U2.1 (AC1)
/OPTO_K: R4.1, U2.2 (AC2)
/SENSE: C1.1, R5.1, U2.4 (C), U3.2 (A)
GND: C1.2, C2.2, C3.1, D1.1 (K), SW1.2, U1.3 (GND), U1.8 (GND), U1.13 (GND), U1.18 (GND), U1.23 (GND), U1.28 (GND), U1.33 (AGND), U1.38 (GND), U2.3 (E), U3.3 (GND), U4.4 (GND), U4.5 (A2), U4.6 (A1), U4.7 (A0)

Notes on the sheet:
W5500-EVB-Pico-PoE (plugs into 2x 1x20 female headers)
GP16..GP21 are used by the on-board W5500 - do not use. GP27 (pin 32) = MAINS_OK input: HIGH = 230VAC present. GP4/GP5 = I2C0 SDA/SCL to TMP1075 (address 0x48). GP22 (pin 29) = SW1 to GND: hold 10 s for a factory reset (internal pull-up). +3V3 comes from the module's 3V3(OUT) pin 36 (PoE powered).
HAZARDOUS VOLTAGE - 230VAC MAINS SENSE
F1 T100mA 250VAC in the only current loop. 4x 68k 1206 (>=200V): ~1.2 mA peak, ~50 mW each. LTV-814S AC-input optocoupler, 5 kVrms. PCB: >=6.5 mm clearance, >=6.4 mm creepage + routed slot.
Mains detect + LED indication (works without firmware)
Opto pulls SENSE low while mains is present; C1 holds it low over the zero crossings (47k x 1uF = 47 ms). MAINS_OK = NOT SENSE: green LED on = mains ON, red LED on = mains OFF.
Temperature sensor TMP1075 (I2C 0x48, +-1 C)
Placed away from the module and the mains resistors. ALERT not used.

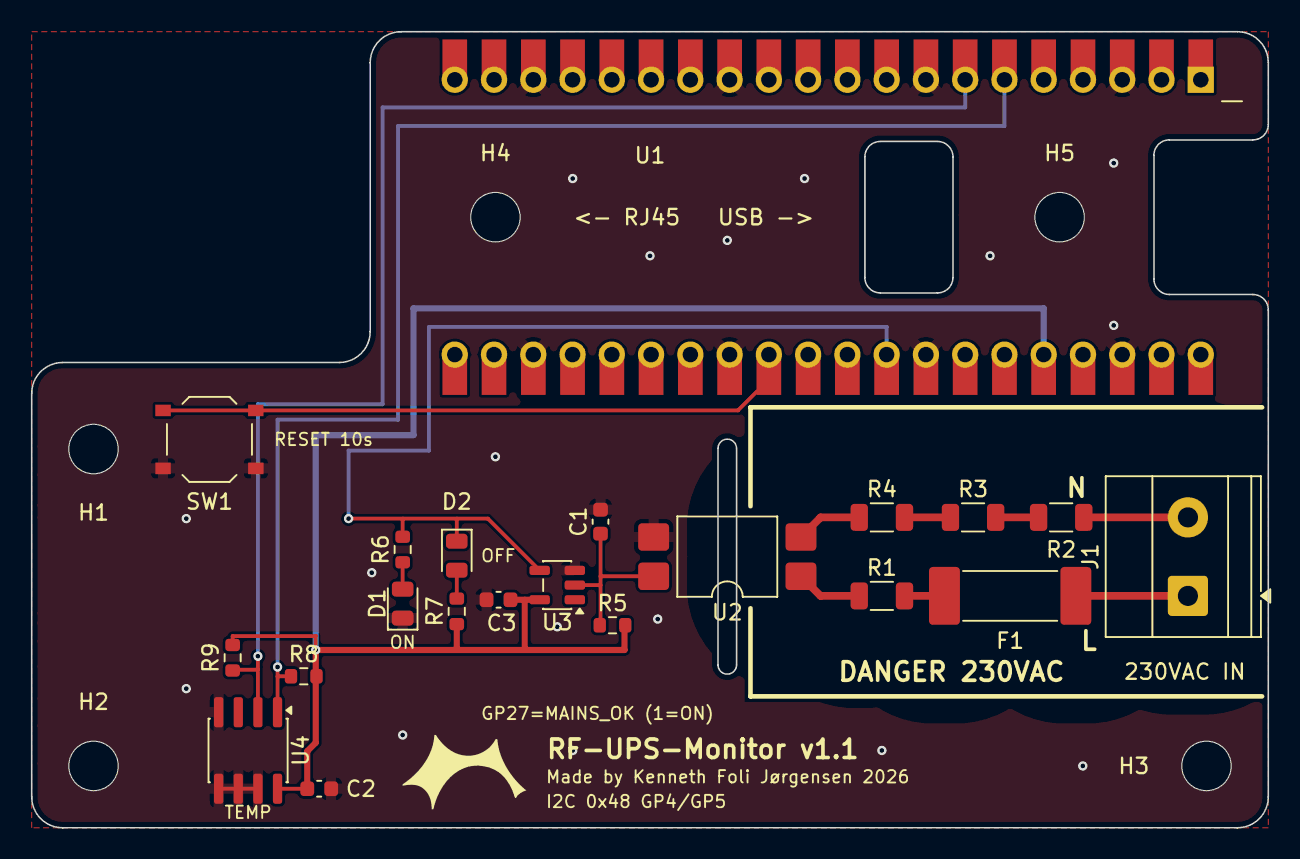
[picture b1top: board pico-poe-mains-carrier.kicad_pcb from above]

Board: 2 copper layers, 80.0 x 51.5 mm, 26 parts (0 on the bottom side), 16 nets.

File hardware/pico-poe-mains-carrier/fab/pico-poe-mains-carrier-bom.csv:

"Designator","Comment","Footprint","LCSC Part #","MPN","Quantity"
"C1","1uF","Capacitor_SMD:C_0603_1608Metric","C15849","","1"
"C2,C3","100nF","Capacitor_SMD:C_0603_1608Metric","C14663","","2"
"D1","Green","LED_SMD:LED_0805_2012Metric","C2297","","1"
"D2","Red","LED_SMD:LED_0805_2012Metric","C84256","","1"
"F1","T100mA 250VAC","Fuse:Fuse_Schurter_UMT250","","Schurter 3403.0156.11 (UMT 250, T 100 mA, 250 VAC)","1"
"J1","230VAC L/N","TerminalBlock_Phoenix:TerminalBlock_Phoenix_MKDS-1,5-2-5.08_1x02_P5.08mm_Horizontal","","Phoenix 1715721 (MKDS 1,5/2-5,08)","1"
"R1-R4","68k 1206 200V","Resistor_SMD:R_1206_3216Metric","C2889820","","4"
"R5","47k","Resistor_SMD:R_0603_1608Metric","C25819","","1"
"R6","100R","Resistor_SMD:R_0603_1608Metric","C22775","","1"
"R7","330R","Resistor_SMD:R_0603_1608Metric","C23138","","1"
"R8,R9","4.7k","Resistor_SMD:R_0603_1608Metric","C23162","","2"
"SW1","FACTORY RESET","Button_Switch_SMD:SW_Push_1P1T_XKB_TS-1187A","C318884","XKB TS-1187A-B-A-B","1"
"U2","LTV-814S","Package_DIP:SMDIP-4_W9.53mm","C125118","LTV-814S-TA1","1"
"U3","SN74LVC1G14DBVR","Package_TO_SOT_SMD:SOT-23-5","C7835","","1"
"U4","TMP1075DR","Package_SO:SOIC-8_3.9x4.9mm_P1.27mm","C2878381","","1"

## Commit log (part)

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2025-02-16 Change the todo
2025-02-18 Version 1
